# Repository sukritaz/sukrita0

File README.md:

# sukrita0
1st eagle cad on tri state buffers

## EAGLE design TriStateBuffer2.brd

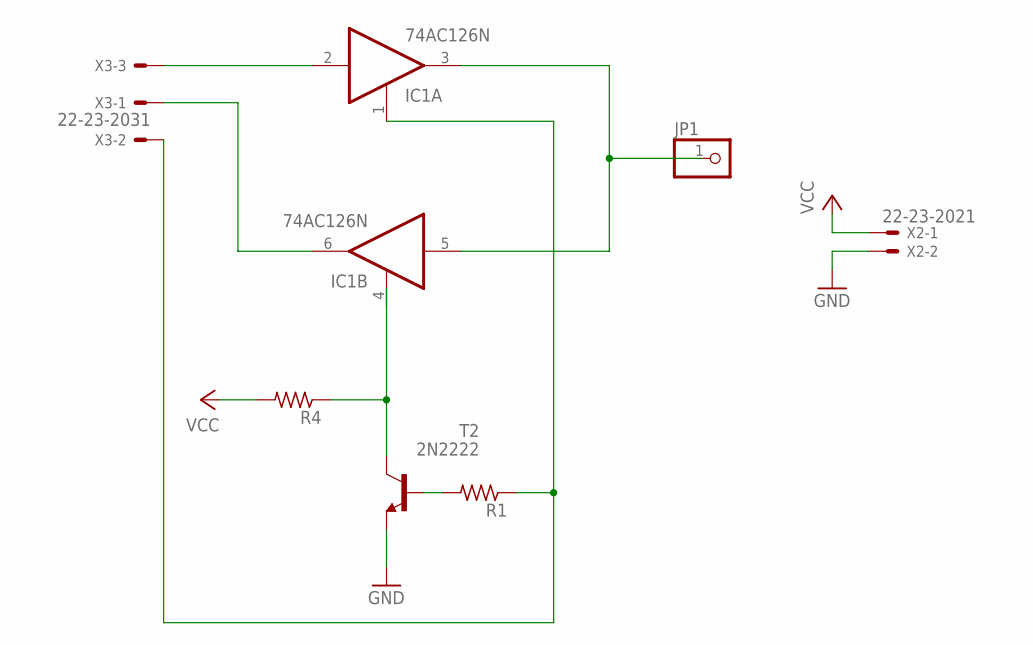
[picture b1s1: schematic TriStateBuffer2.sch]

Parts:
IC1: 74AC126N; DIL14
JP1: PINHD-1X1; 1X01
R1, R4: R-US_0309/12; 0309/12
T2: 2N2222; TO92-EBC-OVAL
X2: 22-23-2021
X3: 22-23-2031

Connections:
GND: IC1.7 (GND), T2.E, X2.2
unnamed: IC1.6 (O), X3.1
unnamed: IC1.2 (I), X3.3
unnamed: IC1.3 (O), IC1.5 (I), JP1.1
unnamed: R1.2, T2.B
unnamed: IC1.4 (OE), R4.1, T2.C
unnamed: IC1.1 (OE), R1.1, X3.2
VCC: IC1.14 (VCC), R4.2, X2.1

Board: 2 copper layers, 7 parts (0 on the bottom side), 8 nets, no tracks yet.
